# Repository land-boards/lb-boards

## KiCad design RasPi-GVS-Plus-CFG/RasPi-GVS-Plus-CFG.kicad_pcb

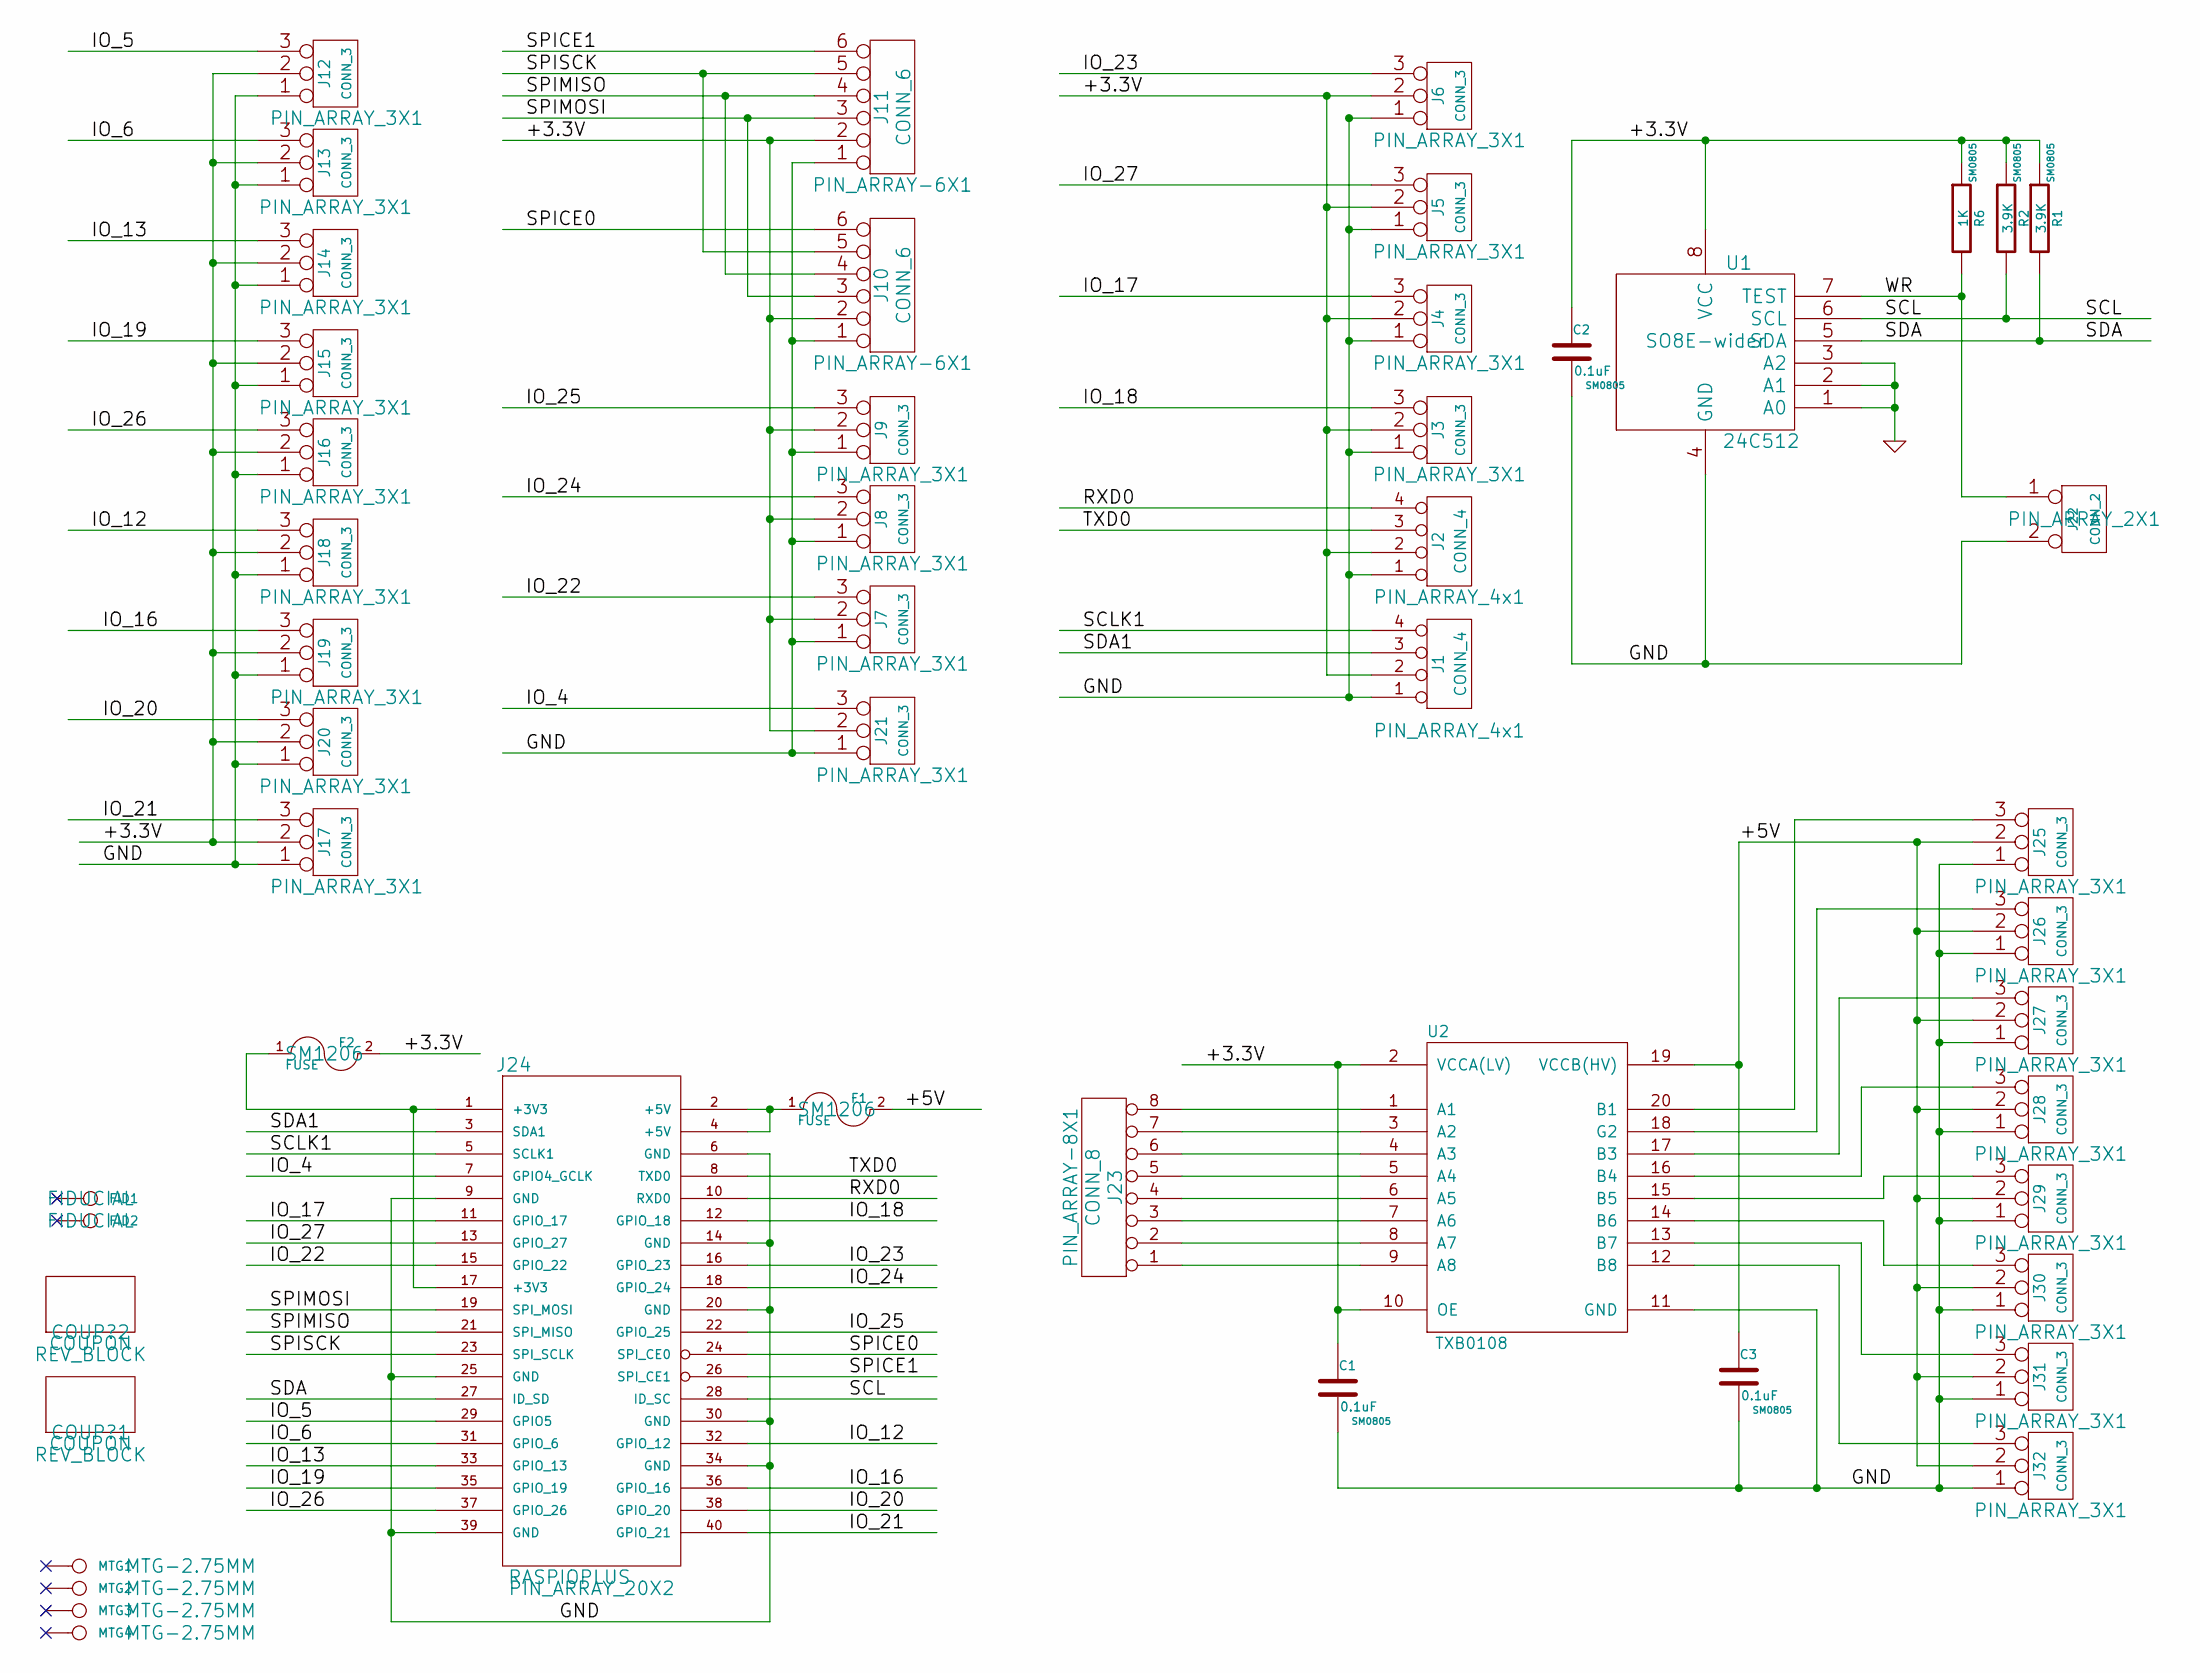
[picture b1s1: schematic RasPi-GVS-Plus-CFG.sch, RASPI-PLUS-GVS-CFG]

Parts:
C1, C2, C3: 0.1uF; SM0805
COUP?1, COUP?2: COUPON; REV_BLOCK
F1, F2: FUSE; SM1206
FID1, FID2: CONN_1; FIDUCIAL
J1, J2: CONN_4; PIN_ARRAY_4x1
J3, J4, J5, J6, J7, J8, J9, J12, J13, J14, J15, J16, J17, J18, J19, J20, J21, J25, J26, J27, J28, J29, J30, J31, J32: CONN_3; PIN_ARRAY_3X1
J10, J11: CONN_6; PIN_ARRAY-6X1
J22: CONN_2; PIN_ARRAY_2X1
J23: CONN_8; PIN_ARRAY-8X1
J24: RASPIOPLUS; PIN_ARRAY_20X2
MTG1, MTG2, MTG3, MTG4: CONN_1; MTG-2.75MM
R1, R2: 3.9K; SM0805
R6: 1K; SM0805
U1: 24C512; SO8E-wider
U2: TXB0108; SOG20

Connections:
/+3.3V: C1.1, C2.1, F2.2, J1.2, J2.2, J3.2 (PM), J4.2 (PM), J5.2 (PM), J6.2 (PM), J7.2 (PM), J8.2 (PM), J9.2 (PM), J10.2, J11.2, J12.2 (PM), J13.2 (PM), J14.2 (PM), J15.2 (PM), J16.2 (PM), J17.2 (PM), J18.2 (PM), J19.2 (PM), J20.2 (PM), J21.2 (PM), R1.1, R2.1, R6.1, U1.8 (VCC), U2.2 (VCCA(LV)), U2.10 (OE)
/+5V: C3.1, F1.2, J25.2 (PM), J26.2 (PM), J27.2 (PM), J28.2 (PM), J29.2 (PM), J30.2 (PM), J31.2 (PM), J32.2 (PM), U2.19 (VCCB(HV))
/IO_4: J21.3, J24.7 (GPIO4_GCLK)
/IO_5: J12.3, J24.29 (GPIO5)
/IO_6: J13.3, J24.31 (GPIO_6)
/IO_12: J18.3, J24.32 (GPIO_12)
/IO_13: J14.3, J24.33 (GPIO_13)
/IO_16: J19.3, J24.36 (GPIO_16)
/IO_17: J4.3, J24.11 (GPIO_17)
/IO_18: J3.3, J24.12 (GPIO_18)
/IO_19: J15.3, J24.35 (GPIO_19)
/IO_20: J20.3, J24.38 (GPIO_20)
/IO_21: J17.3, J24.40 (GPIO_21)
/IO_22: J7.3, J24.15 (GPIO_22)
/IO_23: J6.3, J24.16 (GPIO_23)
/IO_24: J8.3, J24.18 (GPIO_24)
/IO_25: J9.3, J24.22 (GPIO_25)
/IO_26: J16.3, J24.37 (GPIO_26)
/IO_27: J5.3, J24.13 (GPIO_27)
/RXD0: J2.4, J24.10 (RXD0)
/SCL: J24.28 (ID_SC), R2.2, U1.6 (SCL)
/SCLK1: J1.4, J24.5 (SCLK1)
/SDA: J24.27 (ID_SD), R1.2, U1.5 (SDA)
/SDA1: J1.3, J24.3 (SDA1)
/SPICE0: J10.6, J24.24 (SPI_CE0)
/SPICE1: J11.6, J24.26 (SPI_CE1)
/SPIMISO: J10.4, J11.4, J24.21 (SPI_MISO)
/SPIMOSI: J10.3, J11.3, J24.19 (SPI_MOSI)
/SPISCK: J10.5, J11.5, J24.23 (SPI_SCLK)
/TXD0: J2.3, J24.8 (TXD0)
/WR: J22.1, R6.2, U1.7 (TEST)
GND: C1.2, C2.2, C3.2, J1.1, J2.1, J3.1, J4.1, J5.1, J6.1, J7.1, J8.1, J9.1, J10.1, J11.1, J12.1, J13.1, J14.1, J15.1, J16.1, J17.1, J18.1, J19.1, J20.1, J21.1, J22.2 (PM), J24.6 (GND), J24.9 (GND), J24.14 (GND), J24.20 (GND), J24.25 (GND), J24.30 (GND), J24.34 (GND), J24.39 (GND), J25.1, J26.1, J27.1, J28.1, J29.1, J30.1, J31.1, J32.1, U1.1 (A0), U1.2 (A1), U1.3 (A2), U1.4 (GND), U2.11 (GND)
unnamed: F2.1, J24.1 (+3V3), J24.17 (+3V3)
unnamed: J26.3, U2.18 (G2)
unnamed: J29.3, U2.15 (B5)
unnamed: J28.3, U2.16 (B4)
unnamed: J27.3, U2.17 (B3)
unnamed: J25.3, U2.20 (B1)
unnamed: J32.3, U2.12 (B8)
unnamed: J31.3, U2.13 (B7)
unnamed: J30.3, U2.14 (B6)
unnamed: F1.1, J24.2 (+5V), J24.4 (+5V)
unnamed: J23.8, U2.1 (A1)
unnamed: J23.7, U2.3 (A2)
unnamed: J23.6, U2.4 (A3)
unnamed: J23.5, U2.5 (A4)
unnamed: J23.4, U2.6 (A5)
unnamed: J23.3, U2.7 (A6)
unnamed: J23.2, U2.8 (A7)
unnamed: J23.1, U2.9 (A8)

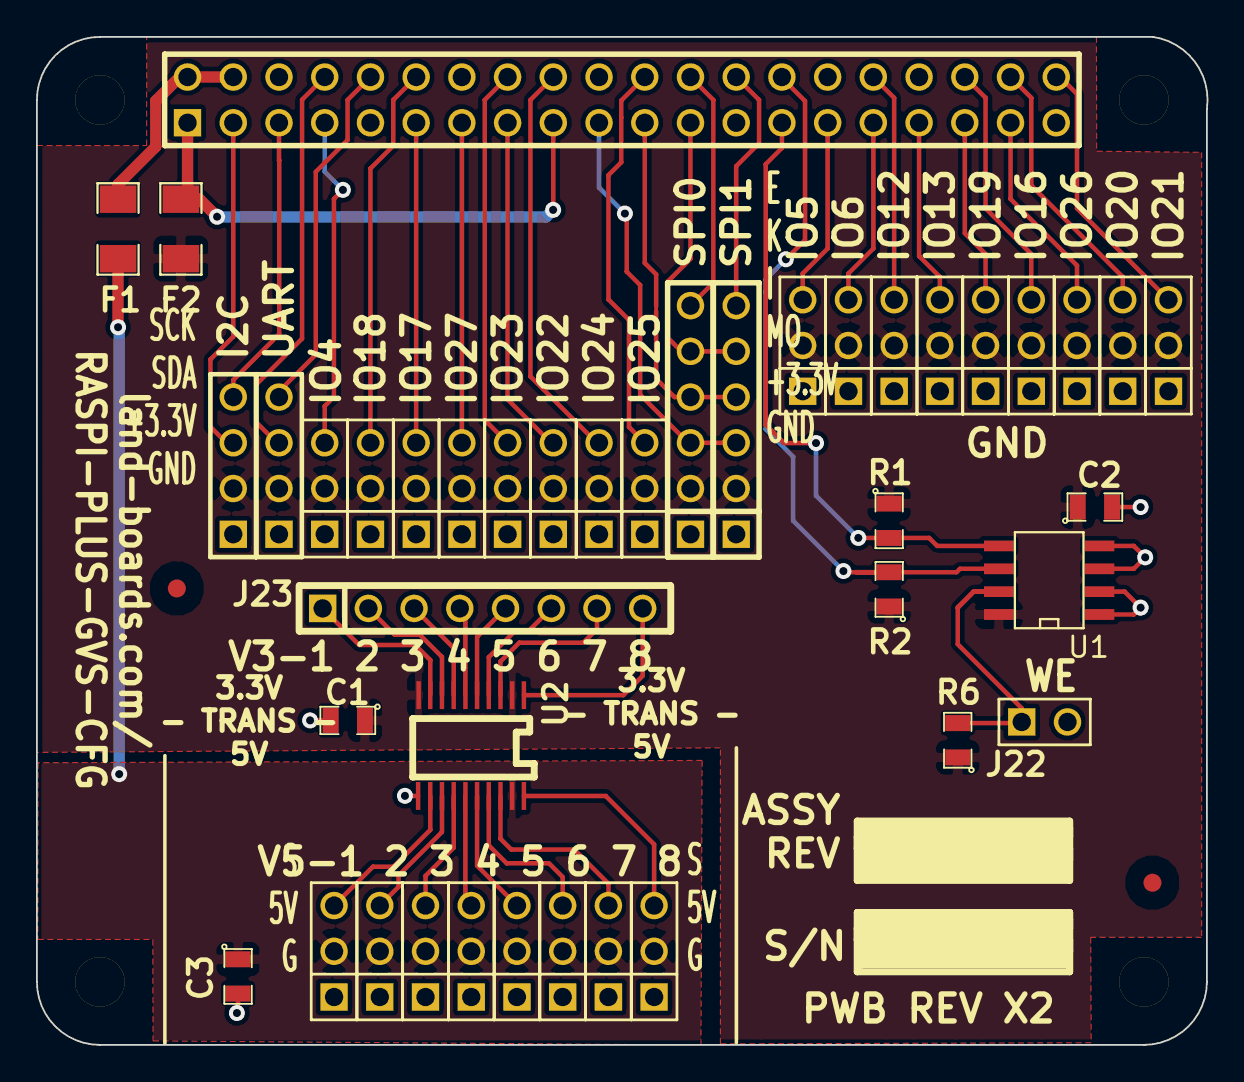
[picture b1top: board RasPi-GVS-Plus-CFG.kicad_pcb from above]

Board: 2 copper layers, 65.0 x 56.0 mm, 50 parts (0 on the bottom side), 50 nets.

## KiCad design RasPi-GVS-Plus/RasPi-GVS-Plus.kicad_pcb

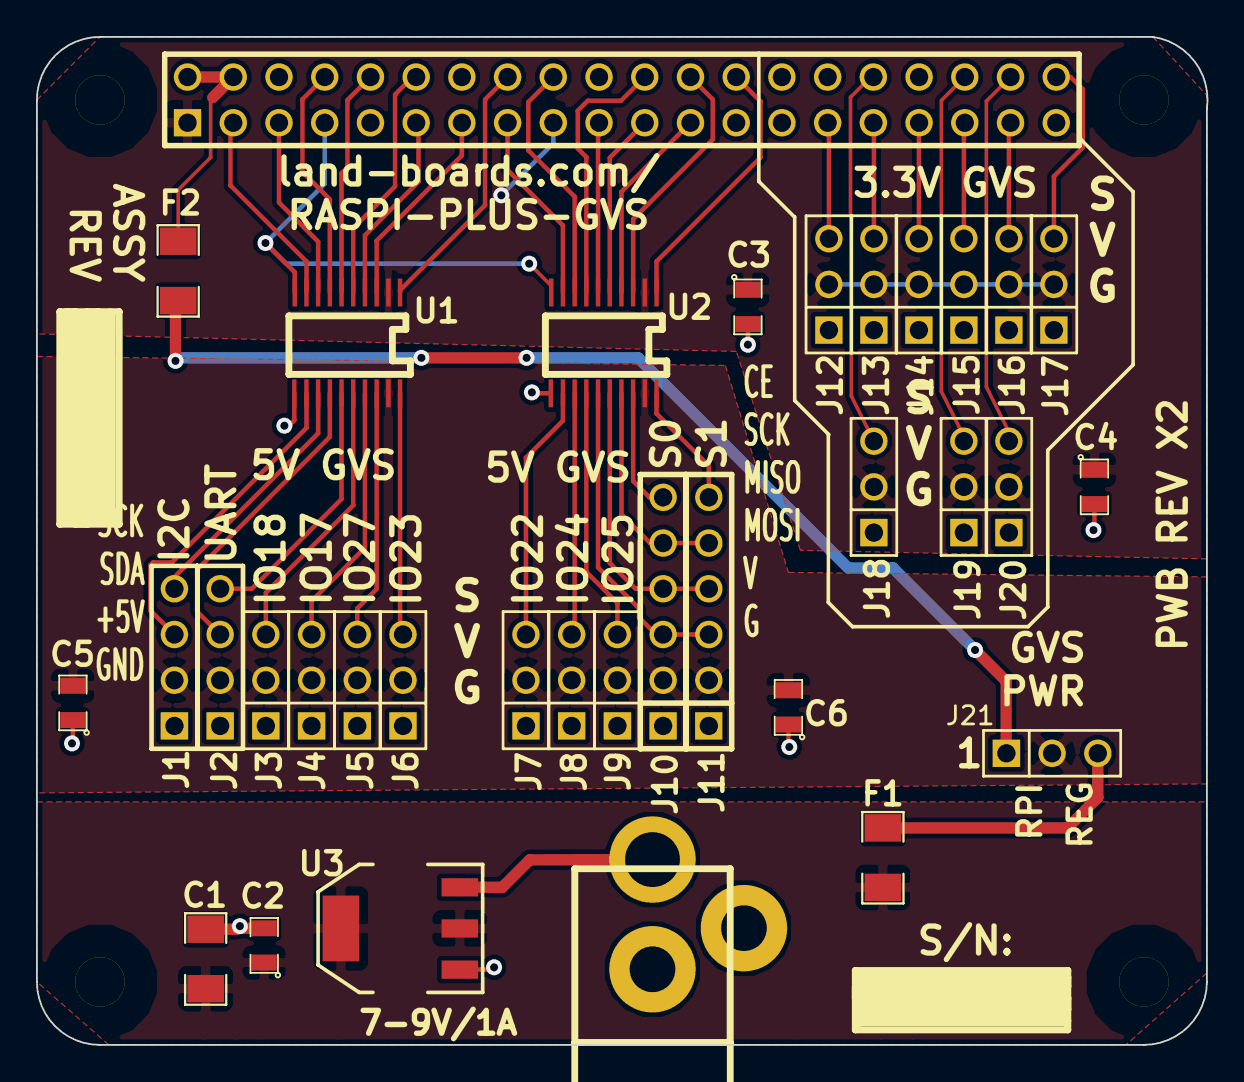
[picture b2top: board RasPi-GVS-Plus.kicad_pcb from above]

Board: 2 copper layers, 65.0 x 56.0 mm, 40 parts (0 on the bottom side), 50 nets.

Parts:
C1: 106; SM1206
C2, C3, C4, C5, C6: 104; SM0805
COUP?1, COUP?2: COUPON; REV_BLOCK
F1, F2: FUSE; SM1206
J1, J2: CONN_4; PIN_ARRAY_4x1
J3, J4, J5, J6, J7, J8, J9, J12, J13, J14, J15, J16, J17, J18, J19, J20, J21: CONN_3; PIN_ARRAY_3X1
J10, J11: CONN_6; PIN_ARRAY-6X1
J22: JACK-3.5MM; JACK_2.1MM
J24: RASPIOPLUS; PIN_ARRAY_20X2
MTG1, MTG2, MTG3, MTG4: CONN_1; MTG-2.75MM
U1, U2: TXB0108; SOG20
U3: AP1117; SOT223

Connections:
/+3.3V: C3.1, C4.1, J12.2, J13.2, J14.2, J15.2, J16.2, J17.2, J18.2, J19.2, J20.2, J24.1, J24.17, U1.2, U2.2
/BIO_17: J4.3, U1.17
/BIO_18: J3.3, U1.16
/BIO_22: J7.3, U2.12
/BIO_23: J6.3, U1.20
/BIO_24: J8.3, U2.13
/BIO_25: J9.3, U2.14
/BIO_27: J5.3, U1.18
/BRXD0: J2.4, U1.15
/BSCLK1: J1.4, U1.13
/BSDA1: J1.3, U1.12
/BSPICE0: J10.6, U2.18
/BSPICE1: J11.6, U2.20
/BSPIMISO: J10.4, J11.4, U2.16
/BSPIMOSI: J10.3, J11.3, U2.15
/BSPISCK: J10.5, J11.5, U2.17
/BTXD0: J2.3, U1.14
/GND: C1.2, C2.2, C3.2, C4.2, C5.1, C6.1, J1.1, J2.1, J3.1, J4.1, J5.1, J6.1, J7.1, J8.1, J9.1, J10.1, J11.1, J12.1, J13.1, J14.1, J15.1, J16.1, J17.1, J18.1, J19.1, J20.1, J22.2, J22.3, J24.6, J24.9, J24.14, J24.20, J24.25, J24.30, J24.34, J24.39, U1.11, U2.11, U3.1
/GV5V: C5.2, C6.2, J1.2, J2.2, J3.2, J4.2, J5.2, J6.2, J7.2, J8.2, J9.2, J10.2, J11.2, J21.2, U1.19, U2.19
/IO_4: J24.7, U1.10, U2.10
/IO_5: J12.3, J24.29
/IO_6: J13.3, J24.31
/IO_12: J18.3, J24.32
/IO_13: J14.3, J24.33
/IO_16: J19.3, J24.36
/IO_17: J24.11, U1.4
/IO_18: J24.12, U1.5
/IO_19: J15.3, J24.35
/IO_20: J20.3, J24.38
/IO_21: J17.3, J24.40
/IO_22: J24.15, U2.9
/IO_23: J24.16, U1.1
/IO_24: J24.18, U2.8
/IO_25: J24.22, U2.7
/IO_26: J16.3, J24.37
/IO_27: J24.13, U1.3
/R5: F2.1, J24.2, J24.4
/RP5V: F2.2, J21.1
/RXD0: J24.10, U1.6
/SCLK1: J24.5, U1.8
/SDA1: J24.3, U1.9
/SPICE0: J24.24, U2.3
/SPICE1: J24.26, U2.1
/SPIMISO: J24.21, U2.5
/SPIMOSI: J24.19, U2.6
/SPISCK: J24.23, U2.4
/TXD0: J24.8, U1.7
/VR5V: F1.2, J21.3
/VRIN: J22.1, U3.3
/VROUT: C1.1, C2.1, F1.1, U3.2, U3.4

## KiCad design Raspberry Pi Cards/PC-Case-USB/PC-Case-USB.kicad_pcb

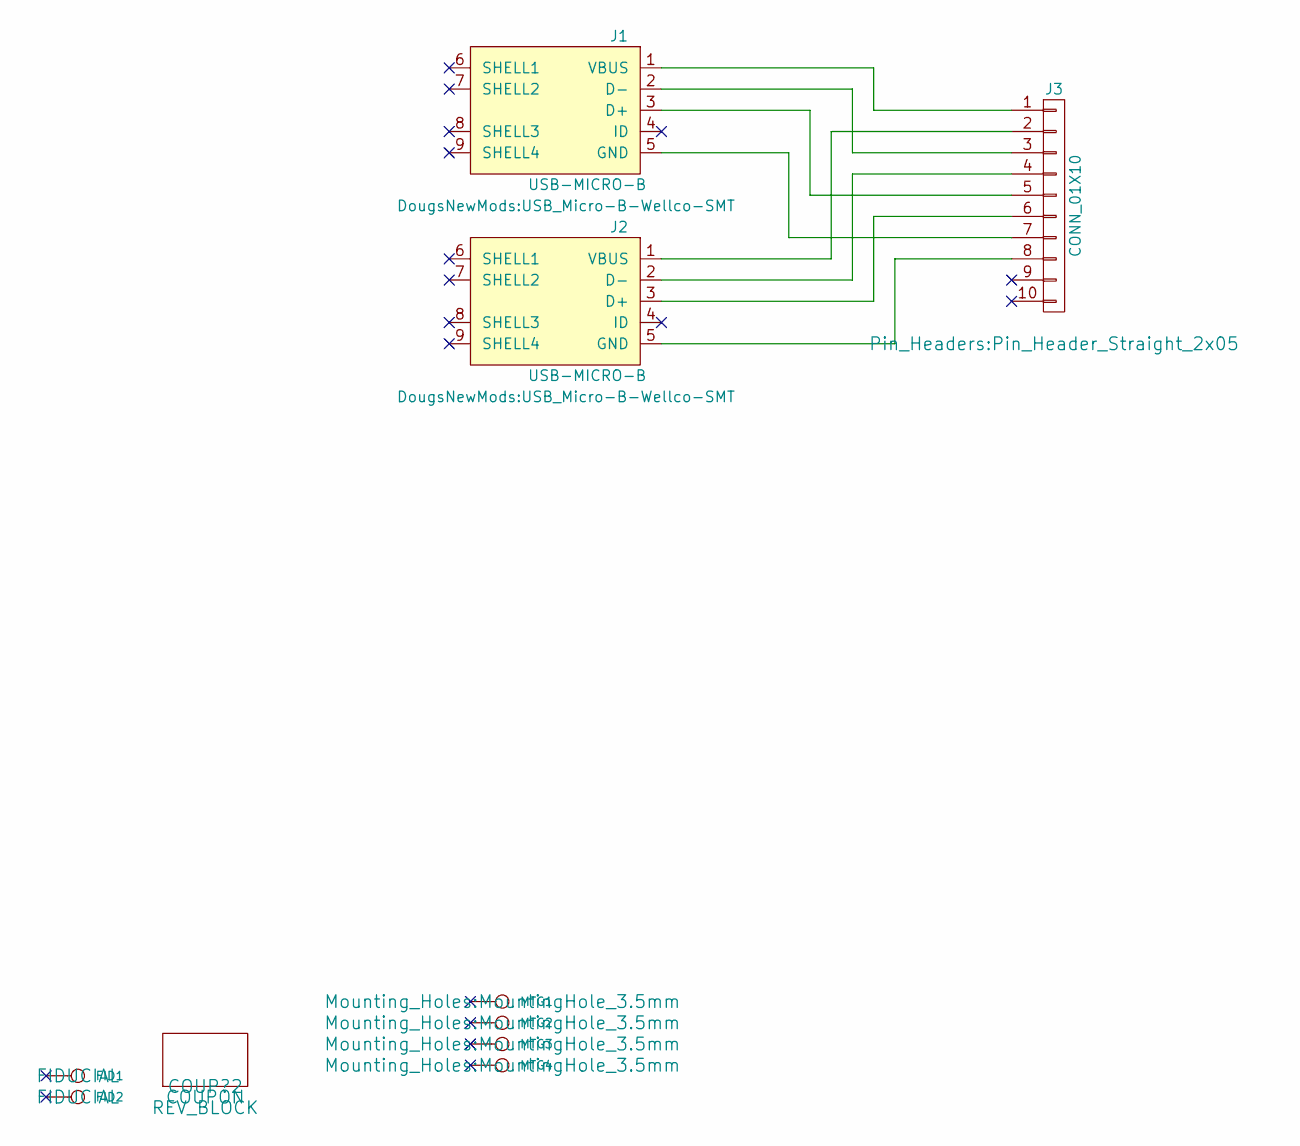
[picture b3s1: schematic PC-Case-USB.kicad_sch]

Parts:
COUP?2: COUPON; REV_BLOCK
FID1, FID2: CONN_1; FIDUCIAL
J1, J2: USB-MICRO-B; USB_Micro-B-Wellco-SMT
J3: CONN_01X10; Pin_Header_Straight_2x05
MTG1, MTG2, MTG3, MTG4: CONN_1; MountingHole_3.5mm

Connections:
unnamed: J1.1 (VBUS), J3.1
unnamed: J1.2 (D-), J3.3
unnamed: J1.3 (D+), J3.5
unnamed: J1.5 (GND), J3.7
unnamed: J2.1 (VBUS), J3.2
unnamed: J2.2 (D-), J3.4
unnamed: J2.3 (D+), J3.6
unnamed: J2.5 (GND), J3.8

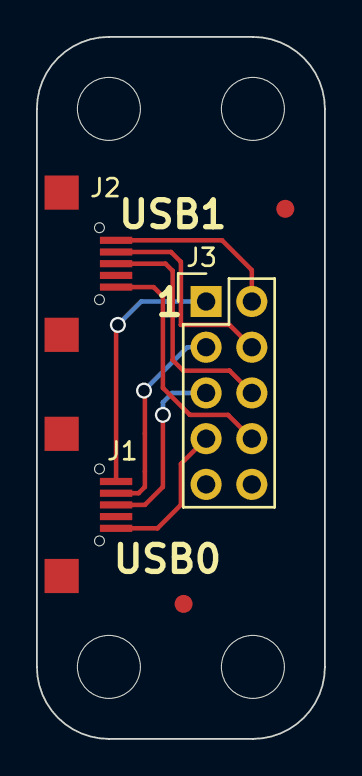
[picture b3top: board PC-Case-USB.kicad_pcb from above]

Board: 2 copper layers, 16.0 x 39.0 mm, 10 parts (1 on the bottom side), 8 nets.

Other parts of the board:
TEST: COUPON; REV_BLOCK

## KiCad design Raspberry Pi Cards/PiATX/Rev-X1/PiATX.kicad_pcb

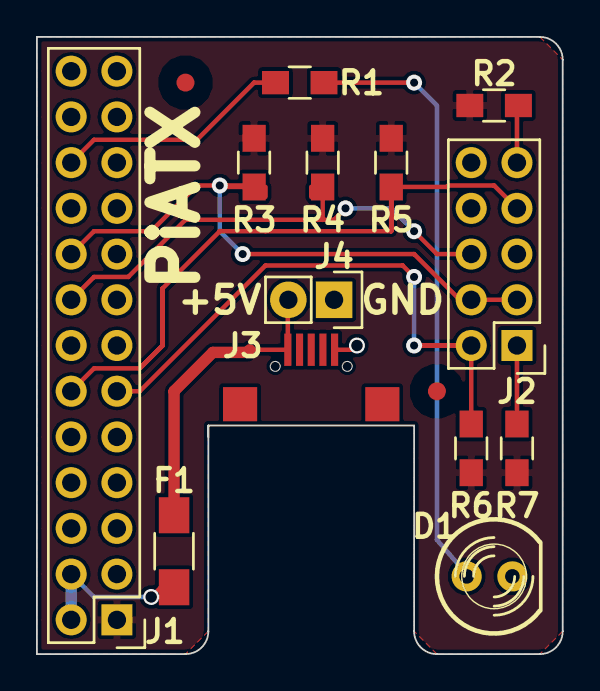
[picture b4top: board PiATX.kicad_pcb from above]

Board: 2 copper layers, 29.2 x 34.3 mm, 16 parts (1 on the bottom side), 12 nets.

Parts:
D1: LED; LED-5MM
F1: FUSE; R_1206_HandSoldering
FID1, FID2: CONN_1; FIDUCIAL
J1: RASPIO; Pin_Header_Straight_2x13
J2: CONN_02X05; Pin_Header_Straight_2x05
J3: USB-MICRO-B; USB_Micro-B-Wellco-SMT
J4: CONN_01X02; Pin_Header_Straight_1x02
R1, R3, R6, R7: 120; R_0805_HandSoldering
R2, R5: DNP; R_0805_HandSoldering
R4: 2.2K; R_0805_HandSoldering
TEST: COUPON; REV_BLOCK

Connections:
+3V3: J1.1, R2.1, R3.1, R4.1, R5.1, R6.1, R7.1
+5V: F1.1, J1.2, J1.4
/FP_PWR_SLP_1: J1.11, J2.2, R6.2
/FP_PWR_SLP_2: J1.18, J2.3, J2.4, R3.2
/HD_LED_P: J2.1, R7.2
/PWR_SW_P: J1.16, J2.6, R4.2
/RST_SW_P: J1.12, J2.7, R5.2
GND: D1.2, J1.6, J1.9, J1.14, J1.20, J1.25, J2.5, J2.8, J3.5, J4.1
unnamed: D1.1, R1.1
unnamed: F1.2, J3.1, J4.2
unnamed: J1.22, R1.2
unnamed: J2.9, R2.2

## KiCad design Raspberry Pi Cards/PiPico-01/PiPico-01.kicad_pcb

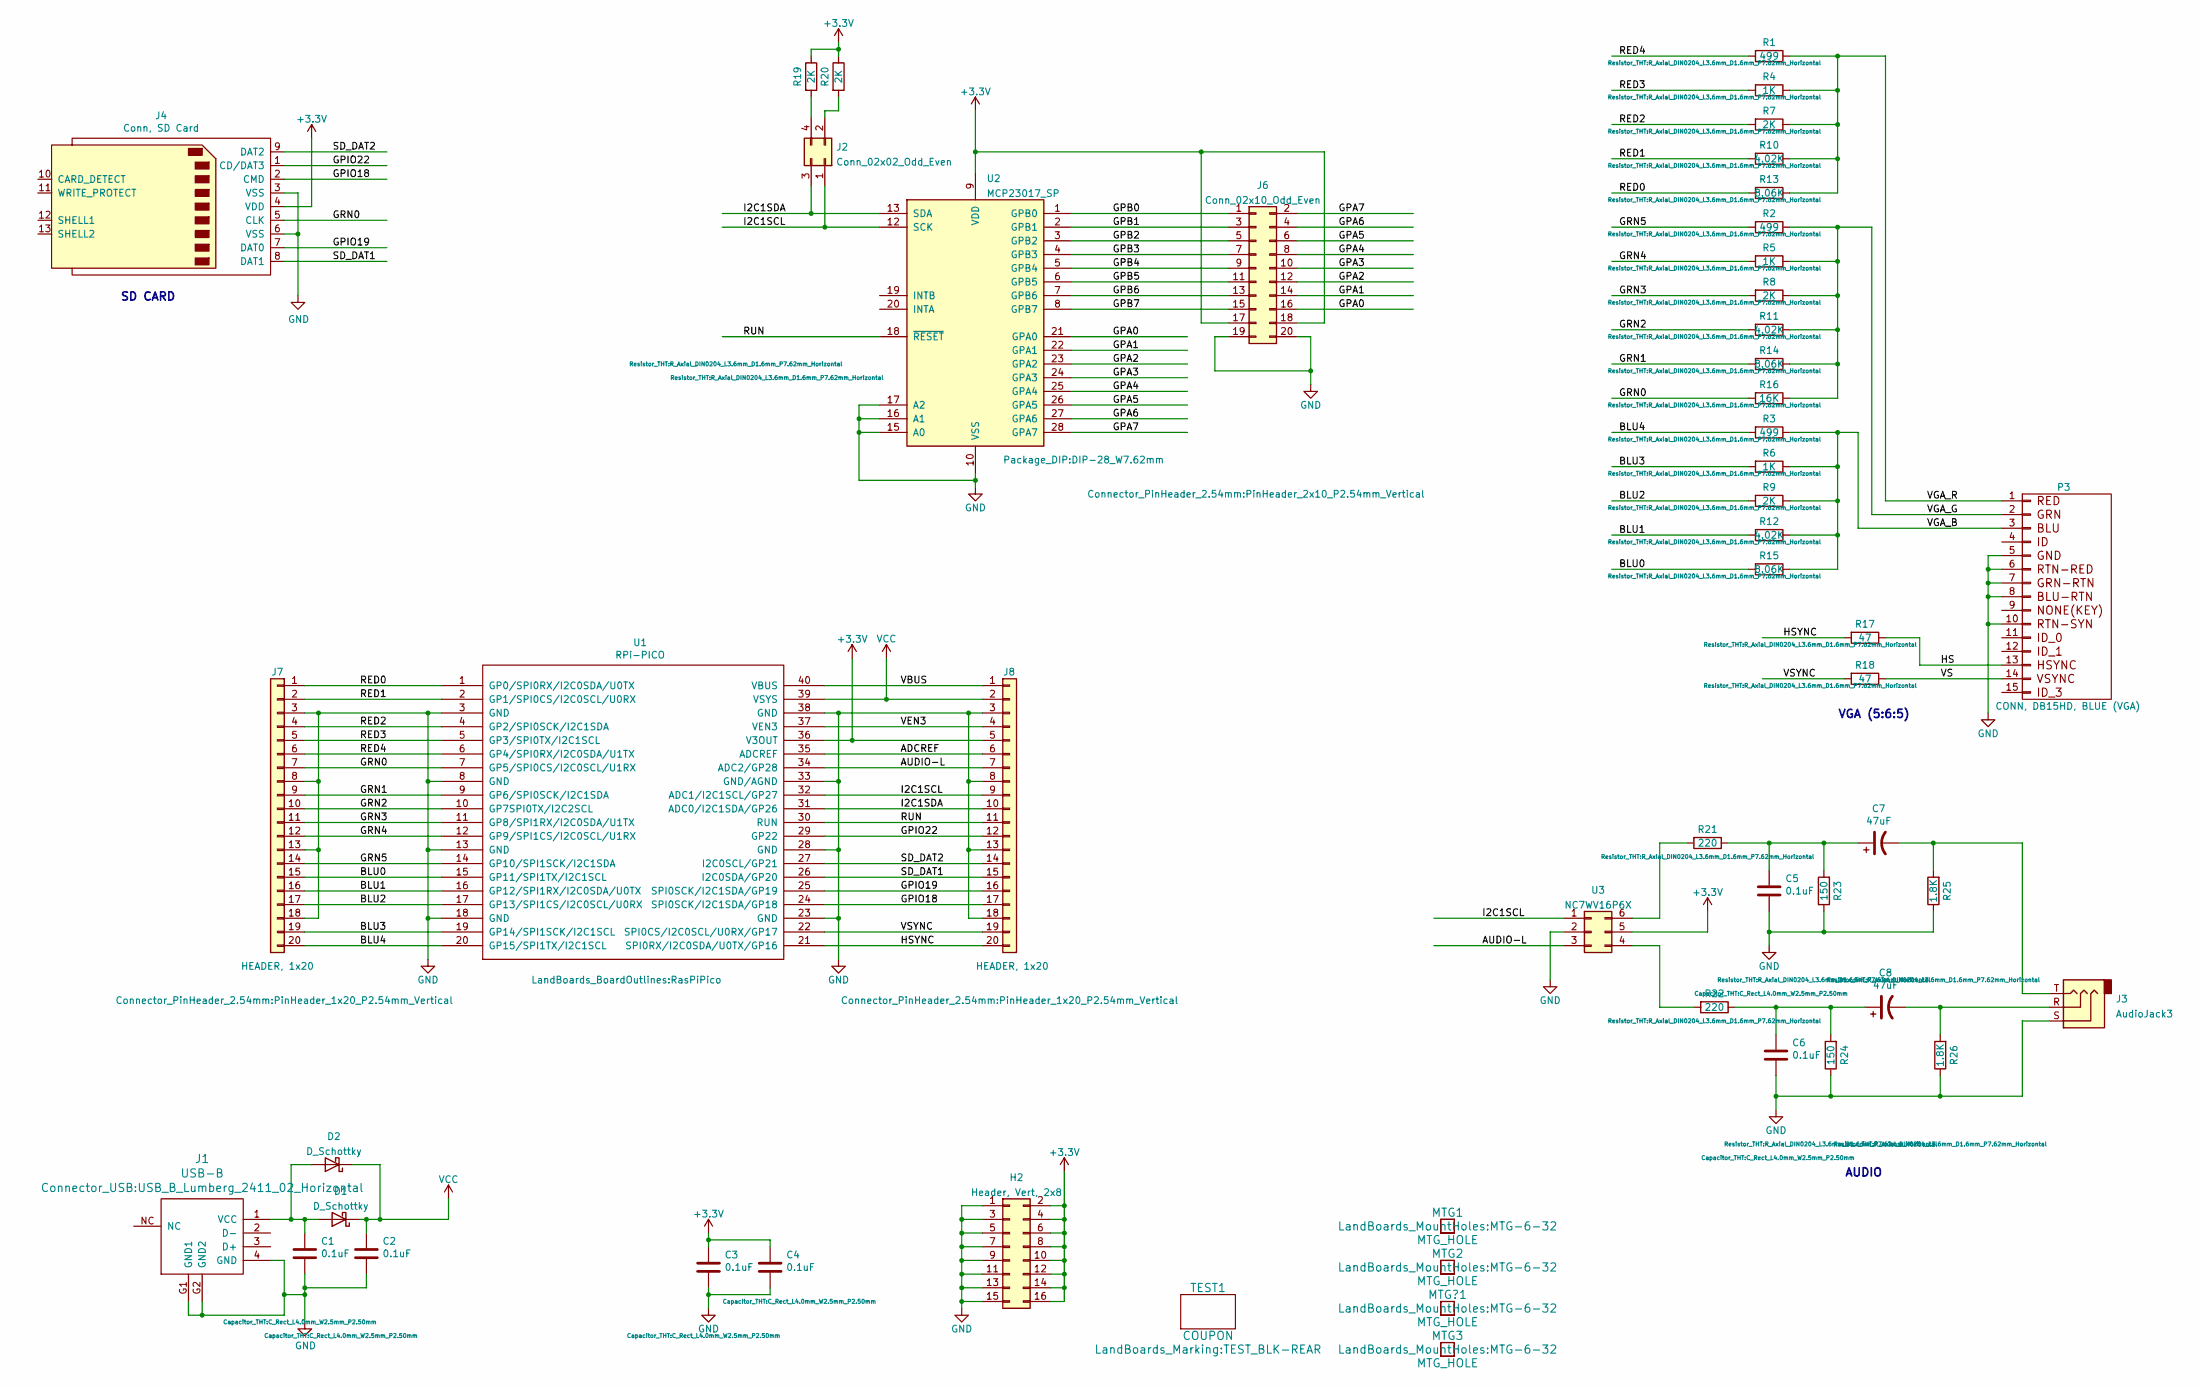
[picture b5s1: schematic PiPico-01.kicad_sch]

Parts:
C1, C2, C3, C4, C5, C6: 0.1uF; C_Rect_L4.0mm_W2.5mm_P2.50mm
C7, C8: 47uF; CP_Radial_D5.0mm_P2.50mm
D1: D_Schottky; D_DO-201AD_P12.70mm_Horizontal
D2: D_Schottky; D_SOD-123
H2: Header, Vert, 2x8; PinSocket_2x08_P2.54mm_Vertical
J1: USB-B; USB_B_Lumberg_2411_02_Horizontal
J2: Conn_02x02_Odd_Even; PinHeader_2x02_P2.54mm_Vertical
J3: AudioJack3; Jack_3.5mm_CUI_SJ1-3523N_Horizontal
J4: Conn, SD Card; SD_CARD
J6: Conn_02x10_Odd_Even; PinHeader_2x10_P2.54mm_Vertical
J7, J8: HEADER, 1x20; PinHeader_1x20_P2.54mm_Vertical
MTG1, MTG2, MTG3: MTG_HOLE; MTG-6-32
MTG?1: MTG_HOLE; MTG-6-32
P3: CONN, DB15HD, BLUE (VGA); DB_15F-VGA-fixed
R1, R2, R3: 499; R_Axial_DIN0204_L3.6mm_D1.6mm_P7.62mm_Horizontal
R4, R5, R6: 1K; R_Axial_DIN0204_L3.6mm_D1.6mm_P7.62mm_Horizontal
R7, R8, R9, R19, R20: 2K; R_Axial_DIN0204_L3.6mm_D1.6mm_P7.62mm_Horizontal
R10, R11, R12: 4.02K; R_Axial_DIN0204_L3.6mm_D1.6mm_P7.62mm_Horizontal
R13, R14, R15: 8.06K; R_Axial_DIN0204_L3.6mm_D1.6mm_P7.62mm_Horizontal
R16: 16K; R_Axial_DIN0204_L3.6mm_D1.6mm_P7.62mm_Horizontal
R17, R18: 47; R_Axial_DIN0204_L3.6mm_D1.6mm_P7.62mm_Horizontal
R21, R22: 220; R_Axial_DIN0204_L3.6mm_D1.6mm_P7.62mm_Horizontal
R23, R24: 150; R_Axial_DIN0204_L3.6mm_D1.6mm_P7.62mm_Horizontal
R25, R26: 1.8K; R_Axial_DIN0204_L3.6mm_D1.6mm_P7.62mm_Horizontal
TEST1: COUPON; TEST_BLK-REAR
U1: RPi-PICO; RasPiPico
U2: MCP23017_SP; DIP-28_W7.62mm
U3: NC7WV16P6X; SC-70-6_Handsoldering

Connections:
+3V3: C3.1, C4.1, H2.2, H2.4, H2.6, H2.8, H2.10, H2.12, H2.14, H2.16, J4.4 (VDD), J6.17, J6.18, J8.5, R19.1, R20.1, U1.36 (V3OUT), U2.9 (VDD), U3.5
/ADCREF: J8.6, U1.35 (ADCREF)
/AUDIO-L: J8.7, U1.34 (ADC2/GP28), U3.3
/BLU0: J7.15, R15.2, U1.15 (GP11/SPI1TX/I2C1SCL)
/BLU1: J7.16, R12.2, U1.16 (GP12/SPI1RX/I2C0SDA/U0TX)
/BLU2: J7.17, R9.2, U1.17 (GP13/SPI1CS/I2C0SCL/U0RX)
/BLU3: J7.19, R6.2, U1.19 (GP14/SPI1SCK/I2C1SCL)
/BLU4: J7.20, R3.2, U1.20 (GP15/SPI1TX/I2C1SCL)
/GPA0: J6.16, U2.21 (GPA0)
/GPA1: J6.14, U2.22 (GPA1)
/GPA2: J6.12, U2.23 (GPA2)
/GPA3: J6.10, U2.24 (GPA3)
/GPA4: J6.8, U2.25 (GPA4)
/GPA5: J6.6, U2.26 (GPA5)
/GPA6: J6.4, U2.27 (GPA6)
/GPA7: J6.2, U2.28 (GPA7)
/GPB0: J6.1, U2.1 (GPB0)
/GPB1: J6.3, U2.2 (GPB1)
/GPB2: J6.5, U2.3 (GPB2)
/GPB3: J6.7, U2.4 (GPB3)
/GPB4: J6.9, U2.5 (GPB4)
/GPB5: J6.11, U2.6 (GPB5)
/GPB6: J6.13, U2.7 (GPB6)
/GPB7: J6.15, U2.8 (GPB7)
/GPIO18: J4.2 (CMD), J8.17, U1.24 (SPI0SCK/I2C1SDA/GP18)
/GPIO19: J4.7 (DAT0), J8.16, U1.25 (SPI0SCK/I2C1SDA/GP19)
/GPIO22: J4.1 (CD/DAT3), J8.12, U1.29 (GP22)
/GRN0: J4.5 (CLK), J7.7, R16.2, U1.7 (GP5/SPI0CS/I2C0SCL/U1RX)
/GRN1: J7.9, R14.2, U1.9 (GP6/SPI0SCK/I2C1SDA)
/GRN2: J7.10, R11.2, U1.10 (GP7SPI0TX/I2C2SCL)
/GRN3: J7.11, R8.2, U1.11 (GP8/SPI1RX/I2C0SDA/U1TX)
/GRN4: J7.12, R5.2, U1.12 (GP9/SPI1CS/I2C0SCL/U1RX)
/GRN5: J7.14, R2.2, U1.14 (GP10/SPI1SCK/I2C1SDA)
/HS: P3.13, R17.1
/HSYNC: J8.20, R17.2, U1.21 (SPI0RX/I2C0SDA/U0TX/GP16)
/I2C1SCL: J2.1, J8.9, U1.32 (ADC1/I2C1SCL/GP27), U2.12 (SCK), U3.1
/I2C1SDA: J2.3, J8.10, U1.31 (ADC0/I2C1SDA/GP26), U2.13 (SDA)
/RED0: J7.1, R13.2, U1.1 (GP0/SPI0RX/I2C0SDA/U0TX)
/RED1: J7.2, R10.2, U1.2 (GP1/SPI0CS/I2C0SCL/U0RX)
/RED2: J7.4, R7.2, U1.4 (GP2/SPI0SCK/I2C1SDA)
/RED3: J7.5, R4.2, U1.5 (GP3/SPI0TX/I2C1SCL)
/RED4: J7.6, R1.2, U1.6 (GP4/SPI0RX/I2C0SDA/U1TX)
/RUN: J8.11, U1.30 (RUN), U2.18 (~RESET)
/SD_DAT1: J4.8 (DAT1), J8.15, U1.26 (I2C0SDA/GP20)
/SD_DAT2: J4.9 (DAT2), J8.14, U1.27 (I2C0SCL/GP21)
/VBUS: J8.1, U1.40 (VBUS)
/VEN3: J8.4, U1.37 (VEN3)
/VGA_B: P3.3, R3.1, R6.1, R9.1, R12.1, R15.1
/VGA_G: P3.2, R2.1, R5.1, R8.1, R11.1, R14.1, R16.1
/VGA_R: P3.1, R1.1, R4.1, R7.1, R10.1, R13.1
/VS: P3.14, R18.1
/VSYNC: J8.19, R18.2, U1.22 (SPI0CS/I2C0SCL/U0RX/GP17)
GND: C1.2, C2.2, C3.2, C4.2, C5.2, C6.2, H2.1, H2.3, H2.5, H2.7, H2.9, H2.11, H2.13, H2.15, J1.4 (GND), J1.G1 (GND1), J1.G2 (GND2), J3.S, J4.3 (VSS), J4.6 (VSS), J6.19, J6.20, J7.3, J7.8, J7.13, J7.18, J8.3, J8.8, J8.13, J8.18, P3.5, P3.6, P3.7, P3.8, P3.10, R23.1, R24.1, R25.1, R26.1, U1.3 (GND), U1.8 (GND), U1.13 (GND), U1.18 (GND), U1.23 (GND), U1.28 (GND), U1.33 (GND/AGND), U1.38 (GND), U2.10 (VSS), U2.15 (A0), U2.16 (A1), U2.17 (A2), U3.2
unnamed: C1.1, D1.2 (A), D2.2 (A), J1.1 (VCC)
unnamed: C5.1, C7.1, R21.1, R23.2
unnamed: C6.1, C8.1, R22.1, R24.2
unnamed: C7.2, J3.T, R25.2
unnamed: C8.2, J3.R, R26.2
unnamed: J2.2, R20.2
unnamed: J2.4, R19.2
unnamed: R21.2, U3.6
unnamed: R22.2, U3.4
VCC: C2.1, D1.1 (K), D2.1 (K), J8.2, U1.39 (VSYS)

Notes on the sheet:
AUDIO
VGA (5:6:5)
SD CARD

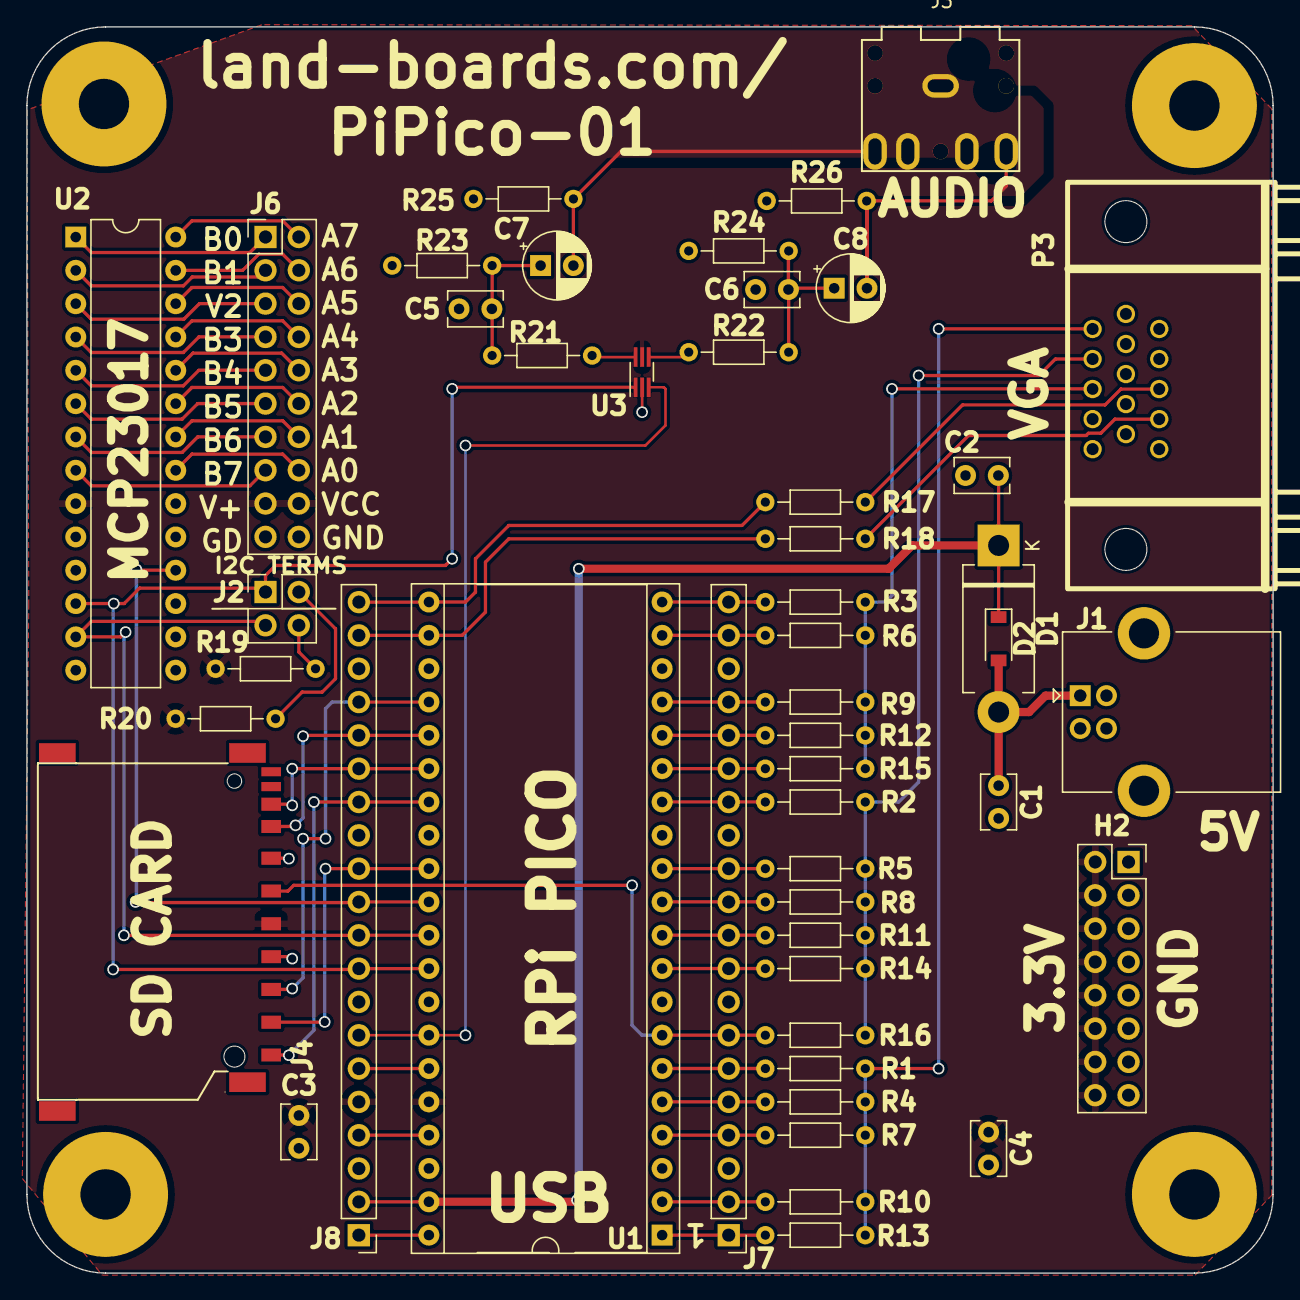
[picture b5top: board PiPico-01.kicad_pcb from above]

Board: 2 copper layers, 95.0 x 95.0 mm, 53 parts (0 on the bottom side), 63 nets.
